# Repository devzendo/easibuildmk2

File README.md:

# EasiBuild Mk II

This repository contains code and documentation for the EasiBuild Mk II low
power (QRP) amateur radio Morse code (CW: Continuous Wave) transceiver designed
by Matt Gumbley M0CUV based on an earlier design by Bruce Edwards G3WCE.

See https://mattgumbley.wordpress.com/category/amateur-radio/easibuild-mk-2/ for
the full set of blog articles on this project.

The code, diagrams, schematics and articles in this project are all licensed
under the Apache Public License, v2.

The Arduino IDE libraries in the Libraries folder are licensed under their own
licenses, please check the zip files there, and their respective websites,
details of which you'll find in the EasiBuildMk2.ino file.

To set up the libraries in the Arduino IDE:
1) SCoop. Create a folder called SCoop in your Arduino IDE's libraries folder
   (e.g. mine is ~/Documents/Arduino/libraries on OSX). Extract the 'SCoop V1.2
   New Year Pack.zip' file to a temporary folder, then copy SCoop/SCoop.{cpp|h}
   into the libraries/SCoop folder you created.
2) LiquidCrystal - can be added as a .zip library.
3) EnableInterrupt - don't know yet....

73 de M0CUV

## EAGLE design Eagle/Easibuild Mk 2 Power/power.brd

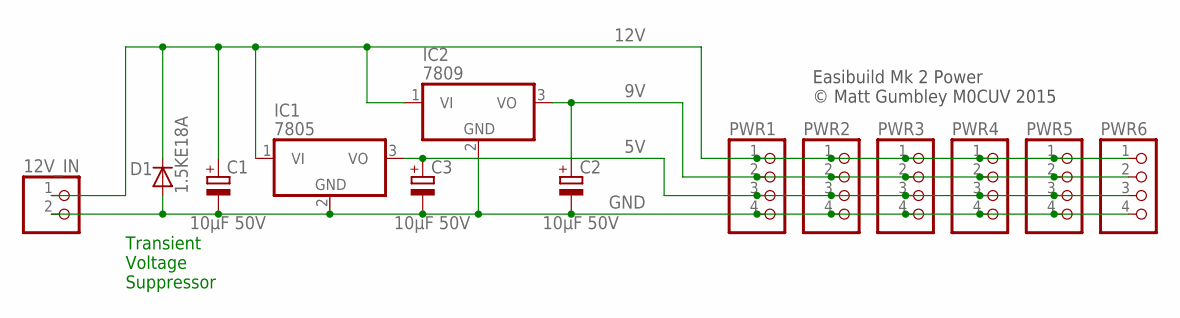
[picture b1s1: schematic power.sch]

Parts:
12V_IN: PINHD-1X2; 1X02
C1, C2, C3: 10μF 50V; E2,5-6E
D1: 1.5KE18A; C1702-254
IC1: 7805; TO220V
IC2: 7809; TO220V
PWR1, PWR2, PWR3, PWR4, PWR5, PWR6: PINHD-1X4; 1X04

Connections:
5V: C3.+, IC1.3 (VO), PWR1.3, PWR2.3, PWR3.3, PWR4.3, PWR5.3, PWR6.3
9V: C2.+, IC2.3 (VO), PWR1.2, PWR2.2, PWR3.2, PWR4.2, PWR5.2, PWR6.2
12V: 12V_IN.1, C1.+, D1.C, IC1.1 (VI), IC2.1 (VI), PWR1.1, PWR2.1, PWR3.1, PWR4.1, PWR5.1, PWR6.1
GND: 12V_IN.2, C1.-, C2.-, C3.-, D1.A, IC1.2 (GND), IC2.2 (GND), PWR1.4, PWR2.4, PWR3.4, PWR4.4, PWR5.4, PWR6.4

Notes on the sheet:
Transient Voltage Suppressor
Easibuild Mk 2 Power © Matt Gumbley M0CUV 2015

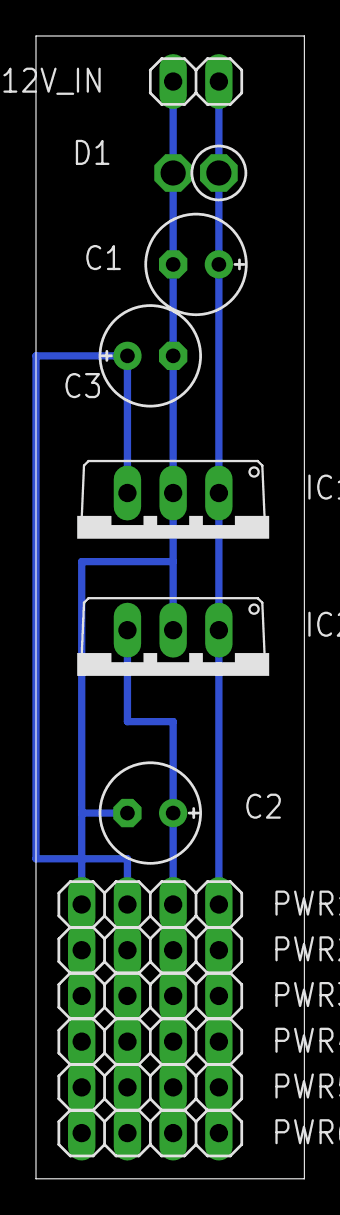
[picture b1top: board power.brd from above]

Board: 2 copper layers, 14.9 x 63.5 mm, 13 parts (0 on the bottom side), 4 nets.

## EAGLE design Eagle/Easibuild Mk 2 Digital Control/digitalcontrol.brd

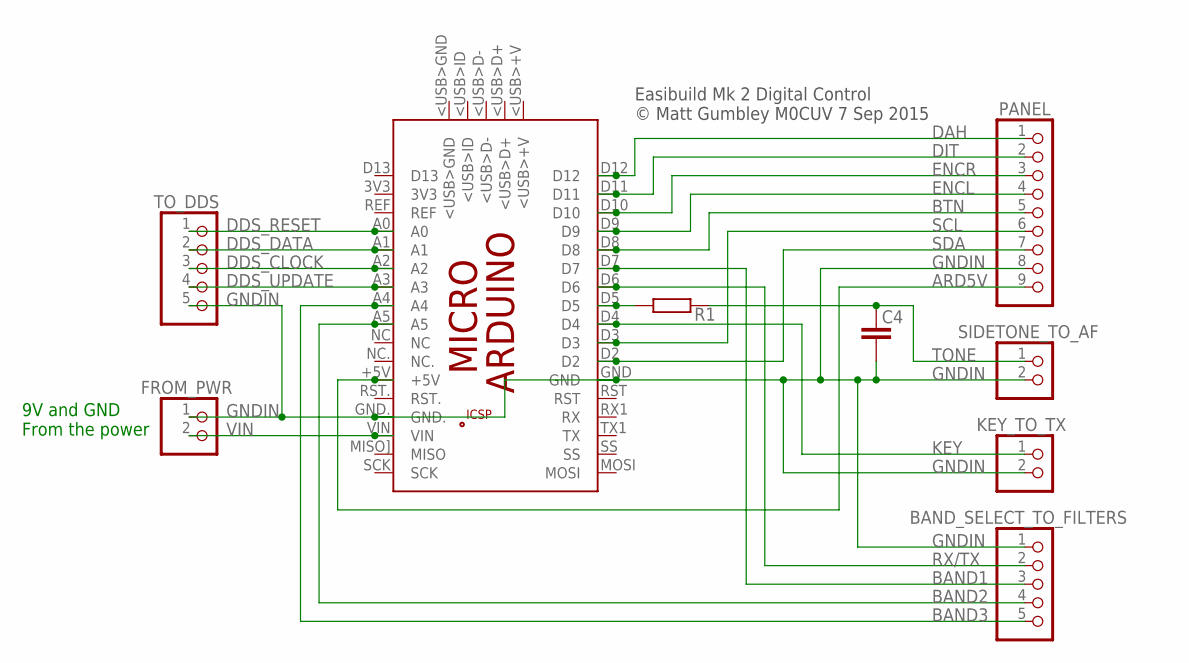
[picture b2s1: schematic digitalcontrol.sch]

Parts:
BAND_SELECT_TO_FILTERS: PINHD-1X5; 1X05
C4: C-EU050-025X075; C050-025X075
FROM_PWR: PINHD-1X2; 1X02
KEY_TO_TX: PINHD-1X2; 1X02
PANEL: PINHD-1X9; 1X09
PCB1: ARDUINO_MICRO
R1: R-EU_0204/5; 0204/5
SIDETONE_TO_AF: PINHD-1X2; 1X02
TO_DDS: PINHD-1X5; 1X05

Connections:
ARD5V: PANEL.9, PCB1.+5V
BAND1: BAND_SELECT_TO_FILTERS.3, PCB1.D7
BAND2: BAND_SELECT_TO_FILTERS.4, PCB1.A5
BAND3: BAND_SELECT_TO_FILTERS.5, PCB1.A4
BTN: PANEL.5, PCB1.D8
DAH: PANEL.1, PCB1.D12
DDS_CLOCK: PCB1.A2, TO_DDS.3
DDS_DATA: PCB1.A1, TO_DDS.2
DDS_RESET: PCB1.A0, TO_DDS.1
DDS_UPDATE: PCB1.A3, TO_DDS.4
DIT: PANEL.2, PCB1.D11
ENCL: PANEL.4, PCB1.D9
ENCR: PANEL.3, PCB1.D10
GNDIN: BAND_SELECT_TO_FILTERS.1, C4.2, FROM_PWR.1, KEY_TO_TX.2, PANEL.8, PCB1.GND, PCB1.GND., SIDETONE_TO_AF.2, TO_DDS.5
KEY: KEY_TO_TX.1, PCB1.D4
unnamed: PCB1.D5, R1.1
RX/TX: BAND_SELECT_TO_FILTERS.2, PCB1.D6
SCL: PANEL.6, PCB1.D3
SDA: PANEL.7, PCB1.D2
TONE: C4.1, R1.2, SIDETONE_TO_AF.1
VIN: FROM_PWR.2, PCB1.VIN

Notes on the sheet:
Easibuild Mk 2 Digital Control © Matt Gumbley M0CUV 7 Sep 2015
9V and GND From the power

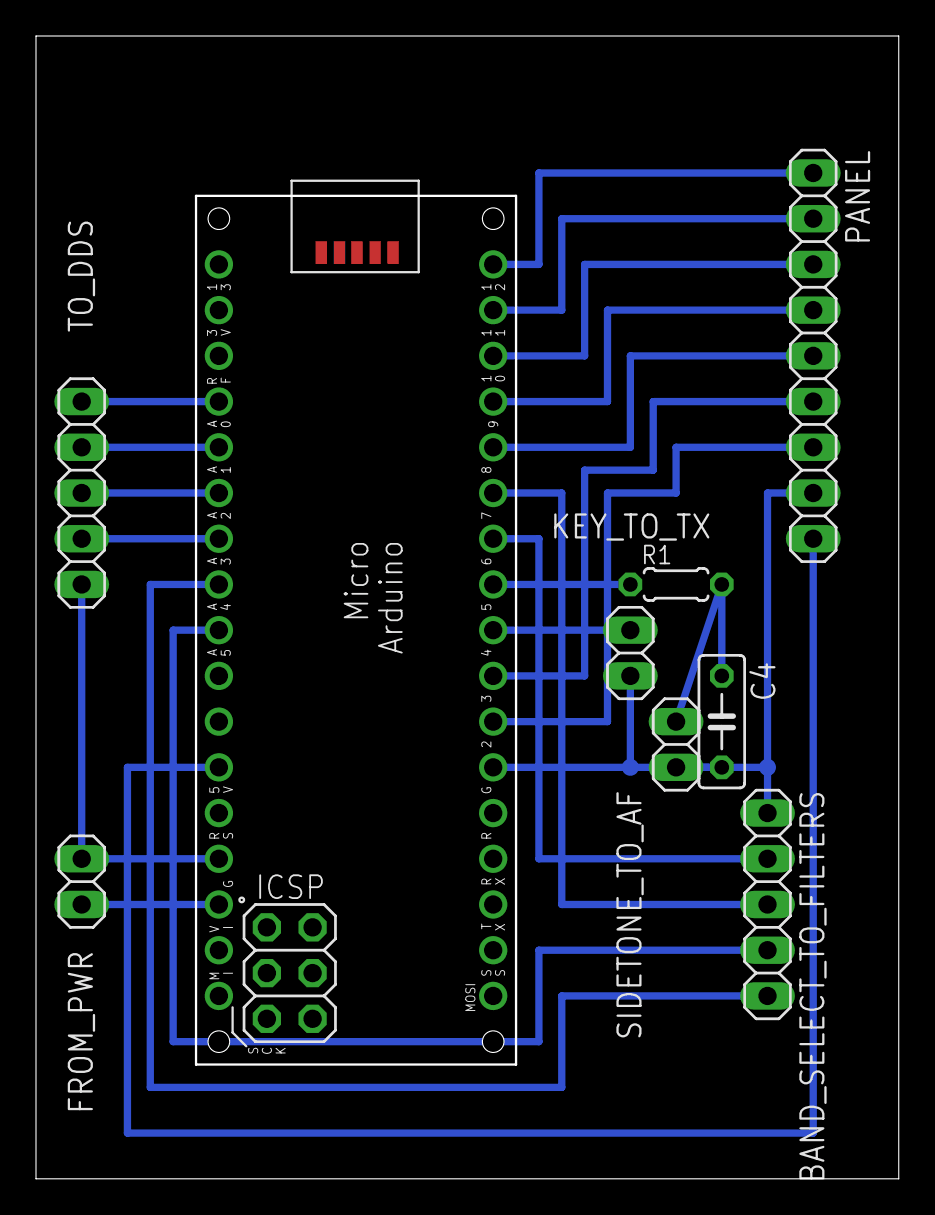
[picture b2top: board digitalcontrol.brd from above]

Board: 1 copper layer, 47.8 x 63.4 mm, 9 parts (0 on the bottom side), 21 nets.

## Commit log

2015-06-20 Initial commit; nothing.....
2015-06-28 Added SCoop, Sine generation, waveform shaping, pin initialisation and main loop that should toggle shaped sinewave. Not yet tested on hardware.
2015-07-02 Switch to sidetone generation using Martin Nawrath's DDS sine wave generator
2015-07-04 Added overview diagram
2015-09-21 The completed power board & schematic.
2015-09-21 What the prototype board looks like.
2015-09-22 Renamed the power board/schematic graphics.
2015-09-22 Add the parts list & other Excel calculations.
2015-09-22 The power board on the breadboard.
2015-09-23 The digital control board schematic, and Arduino Micro pinout (from https://github.com/Bouni/Arduino-Pinout).
2015-09-26 The digital control board layout.
2015-09-28 Pictures of the control board.
2015-09-28 Add a README and the Apache License, v2 under which all files are licensed.
2015-09-28 Rotate the photos!
2015-09-29 Start splitting code out from the main .ino file into reusable modules, for use in the hardware test program.
2015-09-29 Move out the sidetone oscillator code.
2015-09-29 Move out display functions.
2015-09-29 Extract pin I/O and pullup resistor settings to a function.
2015-09-29 Allow compilation of a test harness or the real transceiver.
2015-10-08 Add libraries: enable interrupt, LiquidCrystal, SCoop
2015-10-09 Add notes on installing libraries into the Arduino IDE.
2015-10-16 Add Eagle files for the power board
2015-10-16 Add Eagle files for the digital control board (this version has one of the input pins on port d, not port b)
2015-10-16 The input test harness now shows a legend of inputs, input change count, input values in binary and hex.
2015-10-17 Use PINB and PIND for the input pins. Can't use pin change interrupt to sense DAH, so will use a timer to sample pins.
2015-10-17 Rename the code for the input test harness.
2015-10-17 More test harness definitions, tidy up the input test harness and rename it again.
2015-10-17 Extract pin change sensing.
2015-10-17 Add event handling, at least, an outline of it.
2015-10-17 More test harness work, reading pins inline, event code.
2015-10-17 Bugfix on inputs test harness.
2015-10-17 Now using camelCase for everything… Events test harness, and pin change to event translation (need deb ounce).
2015-10-17 Event handling under 4ms timer control (along with sidetone generation). Test harness writes to serial under timer ISR, which needs decoupling with Scoop.
2015-10-17 Now with rotary encoder decoding!
2015-10-18 Push events onto a SCoop FIFO, rather than calling the dispatch function directly. Pull events off this FIFO in a SCoop task, and write them to serial.
2015-10-18 Sidetone oscillator control test harness.
2015-10-18 The volume is much better going smoothly between [0.0, 0.1]
2015-10-18 Outputs test harness. Untested, compiles.
2015-10-19 First attempt at long press detection event creation.
2015-10-19 Need to invert this state - need to rename it, for clarity: pins are inverted.
2015-10-19 Invert sense of debunker.
2015-10-19 Fast and slow rotary encoder events. Trying to determine cause of strange event codes that occur in the output test harness.
2015-10-20 Some of these pin assignments were wrong...
2015-10-20 This ordering of output pins matches that of the DDS module.
2015-10-21 Pullup resistors mean that inputs are 1=released, 0=pressed. Make note of that.
2015-10-21 Auto loop through the outputs, to help diagnose problems when I have no control board attached - just USB serial monitor.
2015-10-21 The pins have changed their order on the schematic, so reorder them in the test harness.
2015-10-23 A work in progress, thinking out loud, scratching.....
2015-10-23 Correct the left-hand side output pins, with reference to the SDK header. Was working from an incorrect pin mapping diagram.
2015-10-23 Not using enable interrupt library, as I'm sampling all inputs in a timer.
2015-10-23 Ignore debug directory.
2015-10-23 Fix ridiculous error. D'oh. Types, for the win...
2015-10-24 Set the internal LED to output on startup. Will this cause the weak LED on external power-on (not USB) to go away?
2015-10-25 Added a single timer tick event that can be triggered.
2015-10-28 Add the AD9850 module picture.
2015-10-28 Add two Eagle component modules for the Arduino and DDS. Thanks to element14 and Johan Adlers.
2015-10-28 Added the DDS/Buffer board and schematic images.
2015-10-29 Updated control board schematic with values, and rendered at 300dpi
2015-10-29 Get the value and name of the capacitor right, at 300dpi.
2015-10-30 Updated DDS board and schematic with attribution.
2015-10-30 Add the AD9850 DDS module pinout.
2015-11-02 A DDS test harness, untested, compiles. DDS code based on Beric Dunn's analyser code.
2015-11-03 Small refactoring.
2015-11-03 Add schematic of DDS module, from N3ZI http://www.pongrance.com/DDS-9850.html Add AD9850 data sheet.
2015-11-07 Small display fix to the DDS test harness
2015-11-28 Add the N0SS Noise Source schematic and board layout.
2015-11-29 The N0SS noise source, versus dummy load.
2015-11-29 A scan around 20m, showing strong out-of-band signals.
2015-11-30 Copy of Tom N0SS (SK) noise source documentation.
2015-11-30 Noise source, on the scope.
2015-11-30 Noise source, on the scope. (scaled)
2020-03-06 Ensure latest local changes are captured before moving to github.
2020-03-06 These docs and notes need capturing before moving to github
2020-03-09 Migrate to git and github. Remove hg/bitbucket metadata.
